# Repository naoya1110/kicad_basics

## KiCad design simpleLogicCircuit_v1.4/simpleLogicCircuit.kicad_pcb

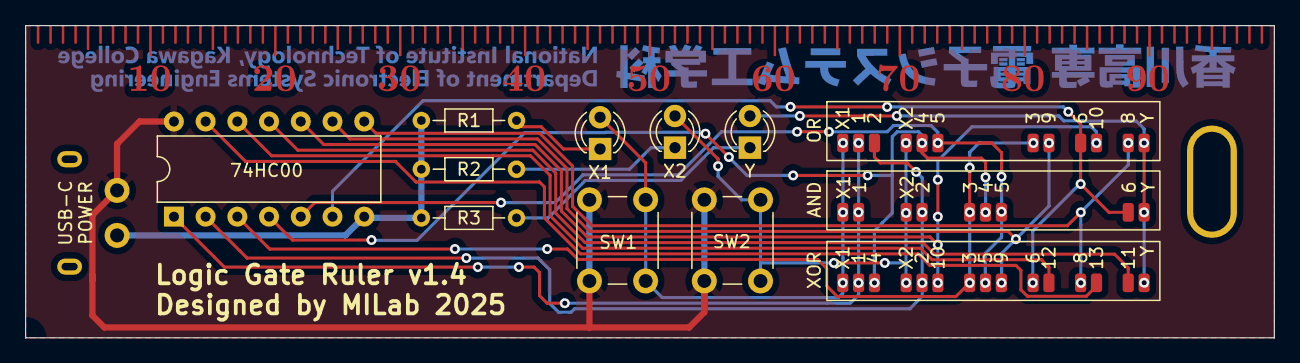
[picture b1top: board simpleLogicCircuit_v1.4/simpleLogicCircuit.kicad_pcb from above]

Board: 2 copper layers, 100.0 x 25.0 mm, 13 parts (0 on the bottom side), 20 nets.

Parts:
74HC00: 74HC00; DIP-14_W7.62mm
AND: Pads_AND; pads_of_and
OR: Pads_OR; pads_of_or
R1, R2, R3: R; R_Axial_DIN0204_L3.6mm_D1.6mm_P7.62mm_Horizontal
SW1, SW2: SW_Push; SW_PUSH_6mm
USB-CPWR: USB_C_Receptacle_PowerOnly_6P; USB-C-A295-CTRPB-1
X1, X2: LED; LED_D3.0mm
XOR: Pads_XOR; pads_of_xor
Y: LED; LED_D3.0mm

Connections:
+5V: 74HC00.14 (VCC), SW1.1, SW2.1, USB-CPWR.A9 (VBUS)
/74HC00-1: 74HC00.1, AND.2, OR.2, XOR.2
/74HC00-2: 74HC00.2, AND.4, OR.3, XOR.5
/74HC00-3: 74HC00.3, AND.5, OR.7, XOR.7
/74HC00-4: 74HC00.4, AND.6, OR.5, XOR.3
/74HC00-5: 74HC00.5, AND.7, OR.6, XOR.8
/74HC00-6: 74HC00.6, AND.8, OR.9, XOR.10
/74HC00-8: 74HC00.8, OR.11, XOR.12
/74HC00-9: 74HC00.9, OR.8, XOR.9
/74HC00-10: 74HC00.10, OR.10, XOR.6
/74HC00-11: 74HC00.11, XOR.14
/74HC00-12: 74HC00.12, XOR.11
/74HC00-13: 74HC00.13, XOR.13
/X1: AND.1, OR.1, SW1.2, X1.2 (A), XOR.1
/X2: AND.3, OR.4, SW2.2, X2.2 (A), XOR.4
/Y: AND.9, OR.12, XOR.15, Y.2 (A)
GND: 74HC00.7 (GND), R1.2, R2.2, R3.2, USB-CPWR.A12 (GND)
unnamed: R1.1, X1.1 (K)
unnamed: R2.1, X2.1 (K)
unnamed: R3.1, Y.1 (K)

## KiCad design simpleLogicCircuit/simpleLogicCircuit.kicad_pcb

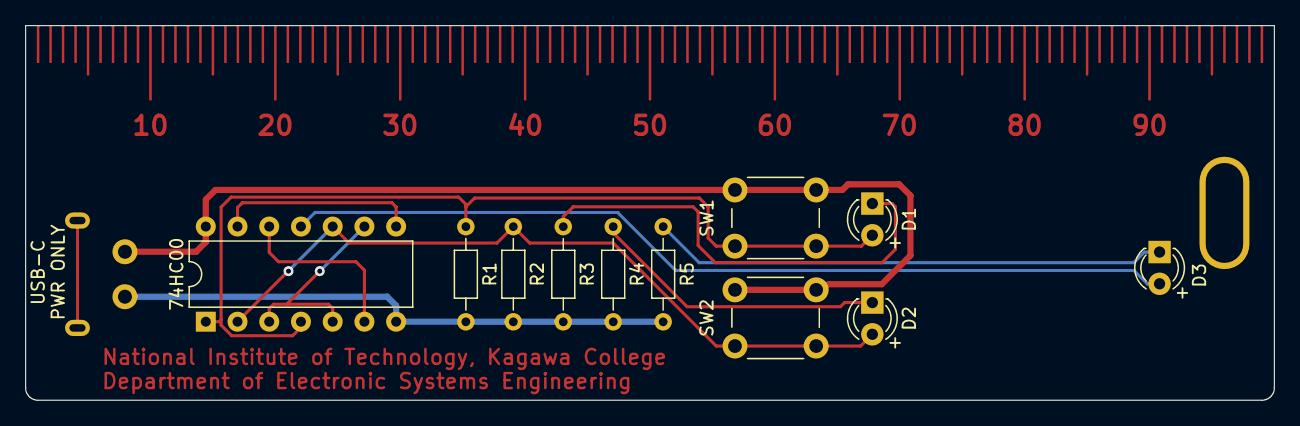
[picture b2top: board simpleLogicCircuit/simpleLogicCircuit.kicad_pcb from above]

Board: 2 copper layers, 100.0 x 30.0 mm, 12 parts (0 on the bottom side), 11 nets.

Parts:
74HC00: 74HC00; DIP-14_W7.62mm
D1, D2, D3: LED; LED_D3.0mm
R1, R2: 10k; R_Axial_DIN0204_L3.6mm_D1.6mm_P7.62mm_Horizontal
R3, R4, R5: R; R_Axial_DIN0204_L3.6mm_D1.6mm_P7.62mm_Horizontal
SW1, SW2: SW_Push; SW_PUSH_6mm
USB-C PWR: USB_C_Receptacle_PowerOnly_6P; USB-C-A295-CTRPB-1

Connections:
+5V: 74HC00.14 (VCC), SW1.1, SW2.1, USB-C PWR.A9 (VBUS)
GND: 74HC00.7 (GND), R1.2, R2.2, R3.2, R4.2, R5.2, USB-C PWR.A12 (GND)
unnamed: D1.1 (K), R3.1
unnamed: 74HC00.1, 74HC00.4, D1.2 (A), R1.1, SW1.2
unnamed: D2.1 (K), R4.1
unnamed: 74HC00.2, 74HC00.10, D2.2 (A), R2.1, SW2.2
unnamed: D3.1 (K), R5.1
unnamed: 74HC00.11, D3.2 (A)
unnamed: 74HC00.3, 74HC00.5, 74HC00.9
unnamed: 74HC00.6, 74HC00.12
unnamed: 74HC00.8, 74HC00.13

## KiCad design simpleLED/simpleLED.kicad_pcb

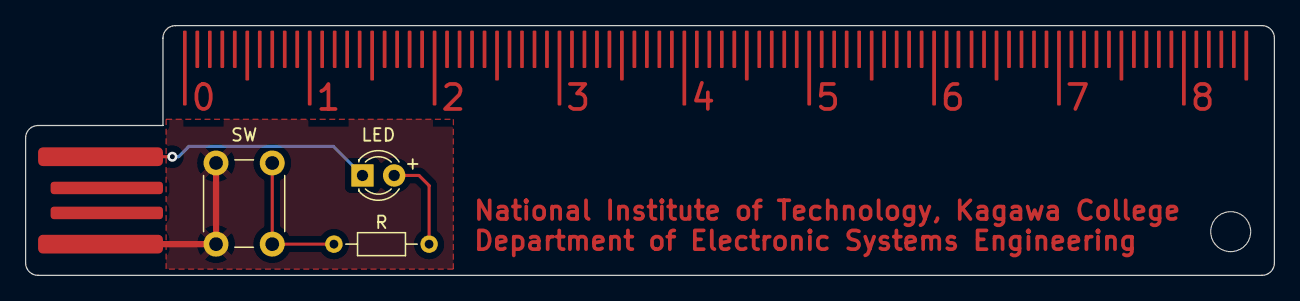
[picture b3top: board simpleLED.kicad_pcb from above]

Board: 2 copper layers, 100.0 x 20.0 mm, 4 parts (0 on the bottom side), 4 nets.

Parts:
LED: LED; LED_D3.0mm
R: R; R_Axial_DIN0204_L3.6mm_D1.6mm_P7.62mm_Horizontal
SW: SW_Push; SW_PUSH_6mm
USB: USB_A; USB-A-Male

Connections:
+5V: SW.1, USB.1 (VBUS)
GND: LED.1 (K), USB.4 (GND)
unnamed: LED.2 (A), R.2
unnamed: R.1, SW.2
